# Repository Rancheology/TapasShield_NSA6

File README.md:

# TapasShield (NSA 6.0)
### Industrial IIoT Boiler Telemetry, Anti-Falsification Ledger & Predictive Maintenance Platform
**Competition:** National Startup Awards 6.0 (NSA 6.0) &bull; Student Innovator (Sub-Category IV: 18+ Years)  
**Track Alignment:** Shakti Ki Sapta Dhara &bull; Stream 1: Manufacturing (Cost, Quality and Scale)  
**Grand Challenge Mandate:** Government of India Ease of Doing Business (EODB) Shared Online Register  
**Statutory Compliance:** Indian Boiler Regulations (IBR 1950 / Rule 392 Continuous Telemetry Revision 2026)  
**Regulatory Authority:** Directorate of Boilers / Central Boilers Board (DPIIT, Ministry of Commerce & Industry)  
**Safety Integrity:** IEC 61508 SIL-2 Hardware Root-of-Trust (ATECC608B + ESP32-S3)  
**Hardware CAD:** KiCad 8 2-Layer Industrial PCB (120mm × 90mm, 0 DRC Errors) & ISO Schematic Blueprint  
**Official Presentation:** 15-Slide Master Deck (`presentation/TapasShield_NSA6_Final_Deck.pdf` & `.pptx`) + 5-Page Visual User Guide (`presentation/TapasShield_Visual_User_Guide.pdf`)

---

## 1. System Overview

TapasShield is a zero-trust industrial IIoT safety, anti-falsification ledger, and predictive maintenance platform designed to eliminate boiler telemetry tampering, prevent catastrophic boiler explosions, and safeguard MSME plants from statutory non-compliance and fuel waste.

It directly solves the core mandate of the **India EODB Grand Challenge**:
> *"Uploads boiler operational telemetry to a secure online register accessible both by the business and the inspecting departments of the State and the Central Government."*

### Key Architecture Components:
1. **Thermodynamic Digital Twin (`backend/boiler_twin.py`)**: Models an industrial fire-tube boiler rated at MAWP = 15.0 bar using exact IAPWS-IF97 steam tables. Translates physical states to industrial $4\text{–}20\text{ mA}$ currents and ADC counts: Channels 1–4 to 16-bit ADS1115 ADC counts and Channel 5 (`AT-101`) to ESP32-S3 12-bit SAR ADC counts over $150.0\,\Omega$ precision shunt resistors.
2. **Edge SIL Node (`backend/edge_sil_node.py`)**: Emulates hardware security element (ATECC608B). Reconstructs engineering units from ADC counts, executes 3 edge security checks (wire-cut $<3.6\text{ mA}$, thermodynamic cross-correlation $|T_{\text{steam}} - T_{\text{sat}}| > 5.0^\circ\text{C}$ or zero-variance clamp, and IBR overpressure/low-water checks), signs canonical RFC 8785 payloads using ECDSA NIST P-256 (`secp256r1`), and maintains a SHA-256 hash chain.
3. **Statutory Inspector Ledger & EODB Engine (`backend/inspector_ledger.py`)**: Immutable zero-trust registry verifying SHA-256 hash chaining and ECDSA digital signatures on every packet. Features:
   - Full forensic audit scanning to pinpoint historical database tampering (`GET /api/ledger/audit`).
   - Multi-State National Industrial Cluster Grid across TN, GJ, MH, and PB (`GET /api/eodb/national-registry`).
   - Dynamically generated and cryptographically signed IBR Form-VI Digital Use Certificates (`GET /api/eodb/certificate`) that auto-renew when compliant and instantly revoke in crimson upon safety or tamper breach.
4. **Predictive Maintenance Engine (`backend/predictive_engine.py`)**: Calculates real-time indirect boiler efficiency per IS 8753 (Siegert formula), fuel financial waste in ₹/hr and ₹/year, $\text{CaCO}_3$ scale thickness, and Remaining Useful Life (RUL) until mandatory statutory descaling.
5. **ESP32-S3 Hardware Firmware (`firmware/src/main.cpp`)**: Production-ready C++ firmware using `mbedtls` ECDSA P-256 and SHA-256, Wokwi simulation configuration (`diagram.json`, `wokwi.toml`), and complete 42-component BOM & pin-to-pin netlist (`hardware/KICAD_BOM_AND_NETLIST.md`).
6. **KiCad 8 PCB & ISO Schematic Blueprint (`hardware/`)**: Complete KiCad 8 board (`tapasshield_edge.kicad_pcb`, 120mm x 90mm) with 16 custom self-contained VRML 2.0 3D models (`hardware/3d_models/`), strict 45°/90° Manhattan routing, verified KiCad 8 CLI DRC (0 airwires, 0 shorts, 0 collisions, 0 clearances), and publication-grade ISO blueprint (`tapasshield_schematic_blueprint.svg`) generated by `hardware/generate_kicad_board.py`.
7. **Official NSA 6.0 Presentation Package (`presentation/`)**: Comprehensive 16:9 widescreen presentation deck (`TapasShield_NSA6_Final_Deck.pdf`, `TapasShield_NSA6_Final_Deck.pptx`) and standalone Visual User Guide (`TapasShield_Visual_User_Guide.pdf`). Features 10 executive business and architecture slides + 5 image-first visual user guides (360° PCB callouts, physical wiring & LTE router architecture, full-screen business SCADA portal, full-screen inspector e-Register, and 4-step quickstart with GitHub QR).
8. **Quint-Cockpit Industrial SCADA & Shared Online Register UI (`frontend/`)**: Vite + React + Tailwind CSS dashboard featuring persistent NSA 6.0 Jury Control Bar with 5 interactive fault scenarios and one-click stakeholder switching:
   - **Dual Split-Screen Live Sync (HERO VIEW)**: MSME Plant Cockpit on left and State & Central Govt Inspector e-Register on right updating simultaneously over WebSockets.
   - **Business Portal (MSME Operator)**: Animated SVG P&ID digital twin, live 5-channel 4–20 mA gauges, IS 8753 efficiency, ₹/hr fuel loss ticker, and scale RUL countdown.
   - **State & Central Govt Inspector Portal**: Central Govt (DPIIT) National Industrial Cluster Grid, State Inspector forensic blockchain ledger, and live IBR Form-VI Digital Certificate modal with instant tamper revocation.
   - **Hardware CAD & Netlist View**: Interactive PCB viewer with layer controls (`F.Cu`, `B.Cu`, `F.SilkS`), blueprint viewer, and searchable 42-item BOM.
   - **NSA 6.0 Pitch Deck View**: Full interactive 16:9 slide player with keyboard navigation, thumbnail strip, `.PPTX` and `.PDF` download buttons, and print export.

---

## 2. Verification Commands

### Full Test Suite (13/13 Tests Passing - 100% Green)
```bash
conda run -n tapasshield-nsa6 pytest tests/
```

### KiCad 8 PCB & Schematic Regeneration & DRC Verification
```bash
conda run -n tapasshield-nsa6 python hardware/generate_kicad_board.py
kicad-cli pcb drc hardware/tapasshield_edge.kicad_pcb --format json --output hardware/drc_report.json
```

### ESP32-S3 C++ Firmware Build (PlatformIO)
```bash
cd firmware
conda run -n tapasshield-nsa6 pio run
```

### React Frontend Production Build (Vite + TypeScript)
```bash
cd frontend
npm run build
```

---

## 3. Launching the Live System

### Backend Server (FastAPI + WebSocket + Static UI)
```bash
conda run -n tapasshield-nsa6 uvicorn backend.main:app --host 0.0.0.0 --port 8000
```
Navigate to `http://localhost:8000` to interact with the full quint-cockpit dashboard and jury controls.

### Frontend Development Server (Hot-Reload Mode)
```bash
cd frontend
npm run dev
```
Navigate to `http://localhost:5173`.

---

## 4. Quick Start (Clone & Run Anywhere)

Run the complete TapasShield stack locally (requires Python 3.10+ and Node.js 18+):

```bash
git clone https://github.com/Rancheology/TapasShield_NSA6.git
cd TapasShield_NSA6
pip install -r requirements.txt
cd frontend && npm install && npm run build && cd ..
uvicorn backend.main:app --host 0.0.0.0 --port 8000
```

Open http://localhost:8000 in your browser to access the live Dual-Access Online Register.

### Run Verification Test Suite
```bash
pytest tests/
```

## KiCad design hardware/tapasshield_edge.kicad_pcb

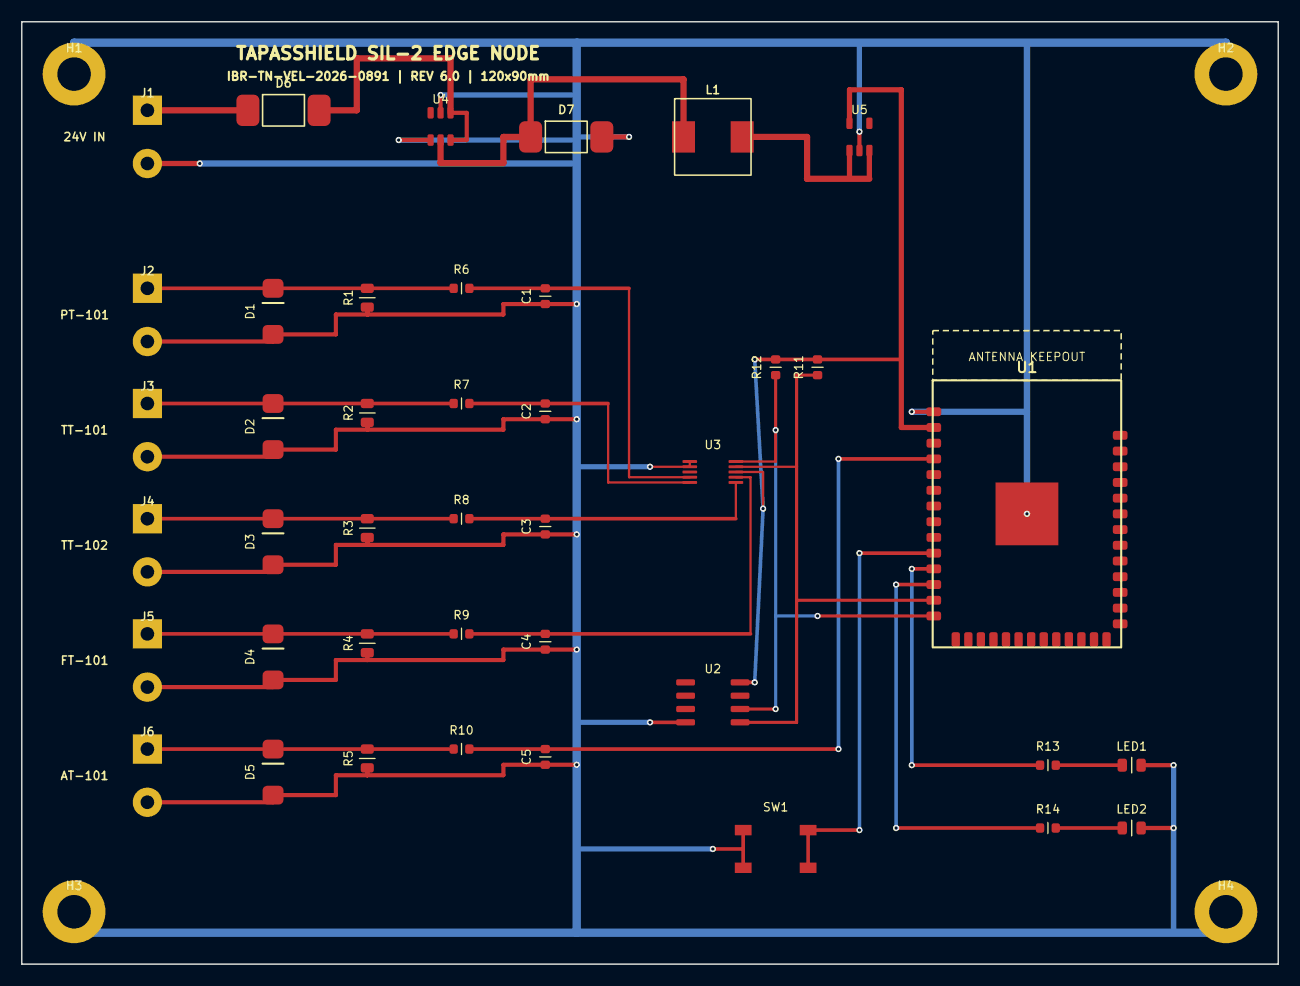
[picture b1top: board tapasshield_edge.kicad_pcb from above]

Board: 2 copper layers, 120.0 x 90.0 mm, 45 parts (0 on the bottom side), 23 nets.

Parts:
C1, C2, C3, C4, C5: 100nF_50V; C_0603_1608Metric
D1, D2, D3, D4, D5: SMAJ28CA; D_SMA
D6, D7: B540C; D_SMC
H1, H2, H3, H4: MountingHole_3.2mm_M3
J1: 24V_PWR; TerminalBlock_Phoenix_MKDS-1,5-2-5.08_1x02_P5.08mm_Horizont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
J2: PT_101; TerminalBlock_Phoenix_MKDS-1,5-2-5.08_1x02_P5.08mm_Horizont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
J3: TT_101; TerminalBlock_Phoenix_MKDS-1,5-2-5.08_1x02_P5.08mm_Horizont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
J4: TT_102; TerminalBlock_Phoenix_MKDS-1,5-2-5.08_1x02_P5.08mm_Horizont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
J5: FT_101; TerminalBlock_Phoenix_MKDS-1,5-2-5.08_1x02_P5.08mm_Horizont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
J6: AT_101; TerminalBlock_Phoenix_MKDS-1,5-2-5.08_1x02_P5.08mm_Horizont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
L1: 10uH_3.5A; L_7.3x7.3_H4.5
LED1: EMERALD; LED_0805_2012Metric
LED2: CRIMSON; LED_0805_2012Metric
R1, R2, R3, R4, R5: 150R_0.05%; R_0805_2012Metric
R6, R7, R8, R9, R10: 100R_1%; R_0603_1608Metric
R11, R12: 4.7k; R_0603_1608Metric
R13, R14: 220R; R_0603_1608Metric
SW1: PTS645_TAMPER; SW_Push_SPST_NO_Alps_SKRK
U1: ESP32-S3-WROOM-1
U2: ATECC608B; SOIC-8_3.9x4.9mm_P1.27mm
U3: ADS1115IDGSR; MSOP-10_3x3mm_P0.5mm
U4: TPS54302DDCR; SOT-23-6
U5: AP2112K-3.3; SOT-23-5

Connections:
+3V3_CLEAN: R11.1, R12.1, U1.2, U2.8, U3.8, U5.5
+5V: L1.2, U5.1, U5.3
+24V: D6.1, U4.3, U4.4
+24V_IN: D6.2, J1.1
AIN0_PT101: C1.1, R6.2, U3.4
AIN1_TT101: C2.1, R7.2, U3.5
AIN2_TT102: C3.1, R8.2, U3.6
AIN3_FT101: C4.1, R9.2, U3.7
AIN4_AT101: C5.1, R10.2, U1.4
GND: C1.2, C2.2, C3.2, C4.2, C5.2, D1.2, D2.2, D3.2, D4.2, D5.2, D7.2, H1.1, H2.1, H3.1, H4.1, J1.2, J2.2, J3.2, J4.2, J5.2, J6.2, LED1.2, LED2.2, R1.2, R2.2, R3.2, R4.2, R5.2, SW1.1, SW1.3, U1.1, U1.41, U2.4, U3.1, U3.2, U4.1, U4.5, U5.2
I2C_SCL: R12.2, U1.14, U2.6, U3.10
I2C_SDA: R11.2, U1.13, U2.5, U3.9
LED1_ANODE: LED1.1, R13.2
LED2_ANODE: LED2.1, R14.2
LED_GREEN: R13.1, U1.11
LED_RED: R14.1, U1.12
LOOP1_IN: D1.1, J2.1, R1.1, R6.1
LOOP2_IN: D2.1, J3.1, R2.1, R7.1
LOOP3_IN: D3.1, J4.1, R3.1, R8.1
LOOP4_IN: D4.1, J5.1, R4.1, R9.1
LOOP5_IN: D5.1, J6.1, R5.1, R10.1
TAMPER_IN: SW1.2, SW1.4, U1.10
V_SW: D7.1, L1.1, U4.2

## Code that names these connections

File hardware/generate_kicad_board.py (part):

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    lines.append(add_segment(2, (132.5, 63.7), (132.5, 66.3), 0.4))
    lines.append(add_segment(2, (132.5, 66.3), (130.95, 66.3), 0.4)) # U4 Pin 3

    # C. V_SW (Net 21): U4 Pin 2 (130.0, 66.3) -> D7 Pad 1 (138.6, 66.0) -> L1 Pad 1 (153.2, 66.0)
    lines.append(add_segment(21, (130.0, 66.3), (130.0, 68.5), 0.6))
    lines.append(add_segment(21, (130.0, 68.5), (136.0, 68.5), 0.6))
    lines.append(add_segment(21, (136.0, 68.5), (136.0, 66.0), 0.6))
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    lines.append(add_segment(5, (164.0, 110.25), (164.0, 121.905), 0.3))
    lines.append(add_segment(5, (164.0, 121.905), (158.6, 121.905), 0.3)) # U2 Pin 5

    # H. TAMPER_IN (Net 12): SW1 Pad 2 (165.1, 132.2) & Pad 4 (165.1, 135.8) -> U1 Pin 10 (177.1, 105.75)
    lines.append(add_segment(12, (165.1, 135.8), (165.1, 132.2), 0.35))
    lines.append(add_segment(12, (165.1, 132.2), (170.0, 132.2), 0.35))
    lines.append(add_via((170.0, 132.2), net_id=12))
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    lines.append(add_segment(12, (170.0, 105.75), (177.1, 105.75), 0.35)) # U1 Pin 10

    # I. LEDs (Route vertically on B.Cu across Y=110..112, so they NEVER cross I2C on F.Cu!)
    # LED_GREEN (Net 13): U1 Pin 11 (177.1, 107.25) -> R13 Pad 1 (187.25, 126.0)
    lines.append(add_segment(13, (177.1, 107.25), (175.0, 107.25), 0.35))
    lines.append(add_via((175.0, 107.25), net_id=13))
    lines.append(add_segment(13, (175.0, 107.25), (175.0, 126.0), width=0.35, layer="B.Cu"))
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    # LED1_ANODE (Net 22): R13 Pad 2 (188.75, 126.0) -> LED1 Pad 1 (195.1, 126.0)
    lines.append(add_segment(22, (188.75, 126.0), (195.1, 126.0), 0.35))

    # LED_RED (Net 14): U1 Pin 12 (177.1, 108.75) -> R14 Pad 1 (187.25, 132.0)
    lines.append(add_segment(14, (177.1, 108.75), (173.5, 108.75), 0.35))
    lines.append(add_via((173.5, 108.75), net_id=14))
    lines.append(add_segment(14, (173.5, 108.75), (173.5, 132.0), width=0.35, layer="B.Cu"))
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    svg.append('  <text x="1095" y="170" fill="#EC4899" font-family="monospace" font-size="15" font-weight="bold" text-anchor="middle">U2 ATECC608B-SSHDA</text>')
    svg.append('  <text x="1095" y="190" fill="#94A3B8" font-family="monospace" font-size="10" text-anchor="middle">Hardware Secure Element (ECDSA NIST P-256)</text>')
    svg.append('  <text x="940" y="220" fill="#E2E8F0" font-family="monospace" font-size="10">Pin 4: GND | Pin 8: +3.3V Clean</text>')
    svg.append('  <text x="940" y="240" fill="#E2E8F0" font-family="monospace" font-size="10">Pin 5: I2C_SDA (Pulled Up 4.7k to 3V3)</text>')
    svg.append('  <text x="940" y="260" fill="#E2E8F0" font-family="monospace" font-size="10">Pin 6: I2C_SCL (Pulled Up 4.7k to 3V3)</text>')

    # U1 ESP32-S3-WROOM-1
    svg.append('  <rect x="920" y="320" width="350" height="510" fill="#1E293B" stroke="#8B5CF6" stroke-width="2" rx="6"/>')
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        ("Pin 2: 3V3", "Power In (+3.3V DC LDO)", 435),
        ("Pin 4: GPIO4 / ADC1_CH3", "Channel 5 Analog In (AT-101)", 465),
        ("Pin 10: GPIO5 (Tamper)", "Physical Enclosure Interlock (SW1)", 500),
        ("Pin 11: GPIO6 (LED_GREEN)", "Emerald Verified Status Indicator", 535),
        ("Pin 12: GPIO7 (LED_RED)", "Crimson Tamper / Trip Alarm Indicator", 570),
        ("Pin 13: GPIO8 (I2C_SDA)", "Secure Bus Data (U2 Crypto + U3 ADC)", 605),
        ("Pin 14: GPIO9 (I2C_SCL)", "Secure Bus Clock (400 kHz Fast-Mode)", 640),
        ("Pin 19: USB_D-", "Native USB-CDC Telemetry Stream", 675),
        ("Pin 20: USB_D+", "Native USB-CDC Telemetry Stream", 705),
        ("Wi-Fi 802.11 b/g/n", "WPA3 Enterprise MQTT Telemetry", 745),
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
